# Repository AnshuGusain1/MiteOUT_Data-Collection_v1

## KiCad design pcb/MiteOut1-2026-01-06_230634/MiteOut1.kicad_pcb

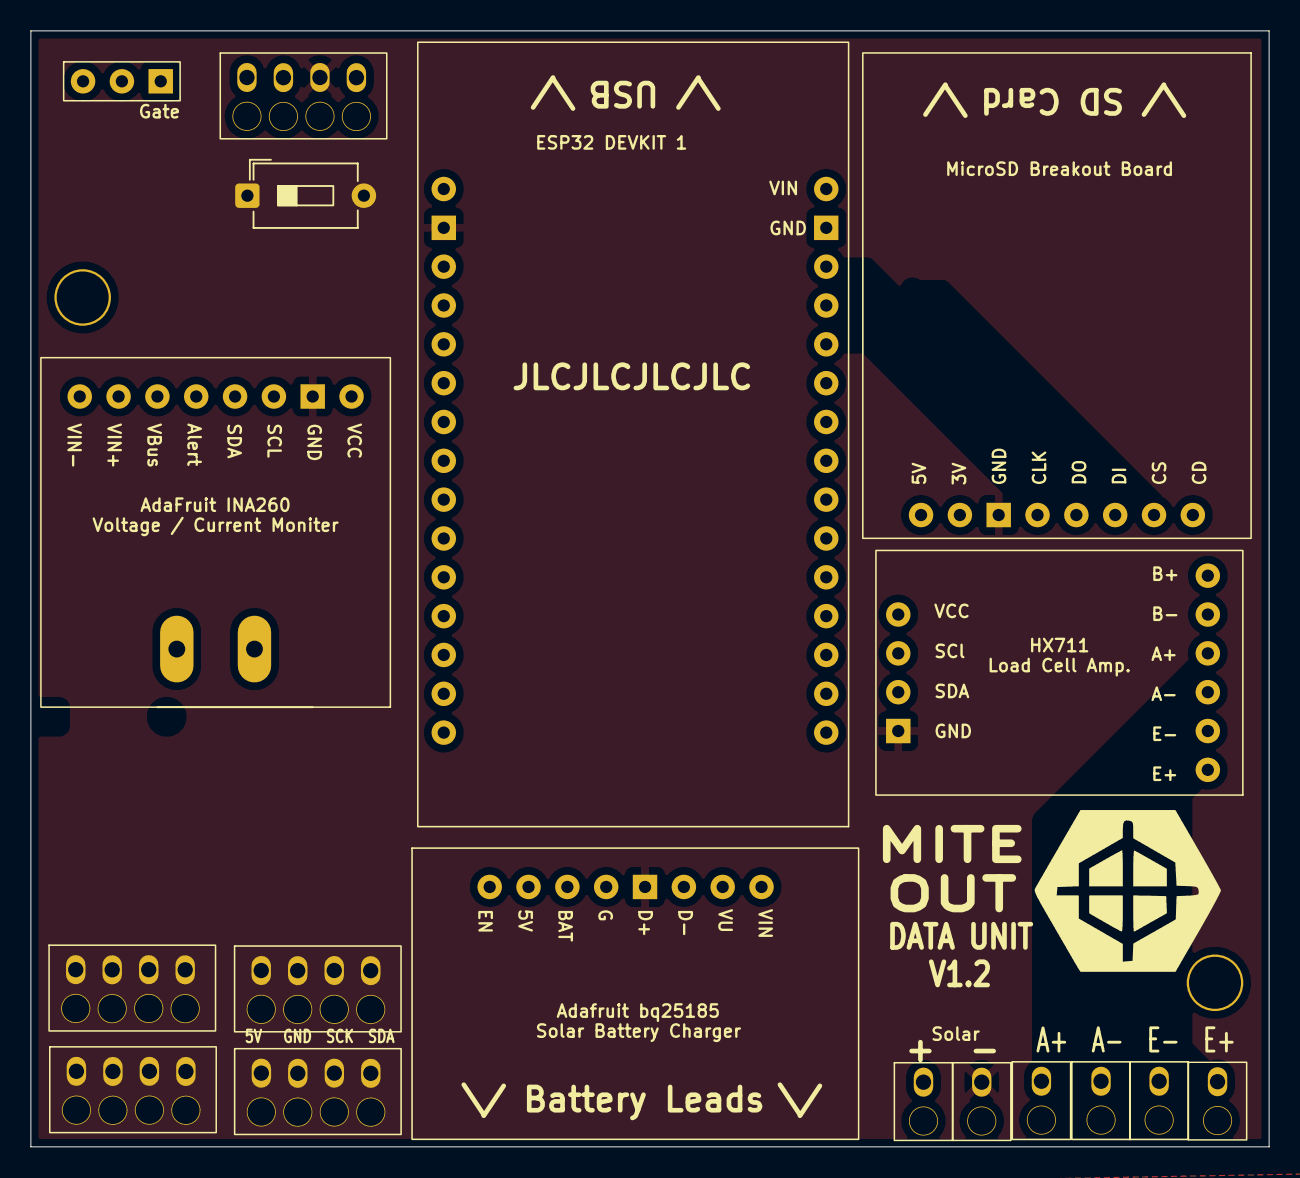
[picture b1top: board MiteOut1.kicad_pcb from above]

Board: 2 copper layers, 81.0 x 73.0 mm, 18 parts (0 on the bottom side), 19 nets, no tracks yet.

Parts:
BME1, BME2, BME3, BME4: Conn_01x04; 4Wire
BQ1: Charger
Clock1: Clock; 4Wire
H1: LoadCell3; throughole
H2: LoadCell1; throughole
H3: LoadCell4; throughole
H4: LoadCell2; throughole
H11: MountingHole_Pad_MP; throughole
H12: Solar -; throughole
HX711: hx711
INO1: INA
J3: Conn_02x15_Counter_Clockwise; ESP
Q1: PMOS; Mosfet
SW2: SW_SPST; SW_DIP_SPSTx01_Slide_6.7x4.1mm_W7.62mm_P2.54mm_LowProfile
U3: SDCard

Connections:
/HX711 CLK: HX711.9 (SCK), J3.9
/HX711 DT: HX711.8 (DT), J3.8
/Sensor VCC: BME1.4, BME2.4, BME3.4, BME4.4, Clock1.4 (3.3v), HX711.10 (VCC), INO1.1 (VCC), INO1.8 (VIN-)
/Wire0 SCK: BME1.2, BME2.2, Clock1.2 (SCL), INO1.3 (SCL), J3.26
/Wire0 SDA: BME1.1, BME2.1, Clock1.1 (SDA), INO1.4 (SDA), J3.29
/Wire1 SCK: BME3.2, BME4.2, J3.6, J3.7
/Wire1 SDA: BME3.1, BME4.1
GND: BME1.3, BME2.3, BME3.3, BQ1.5 (Ground), Clock1.3 (Gnd), H12.MP, HX711.7 (GND), INO1.2 (GND), J3.17, U3.6 (GND)
unnamed: BQ1.7 (5v), SW2.2 (B)
unnamed: BQ1.1 (Solar_in), H11.MP
unnamed: H2.MP, HX711.4 (A+)
unnamed: H1.MP, HX711.3 (A-)
unnamed: H3.MP, HX711.1 (E+)
unnamed: H4.MP, HX711.2 (E-)
unnamed: J3.11, U3.5 (CLK)
unnamed: J3.12, U3.4 (DO)
unnamed: J3.13, U3.3 (DI)
unnamed: J3.15, SW2.1 (A)
unnamed: J3.18, U3.2 (CS)

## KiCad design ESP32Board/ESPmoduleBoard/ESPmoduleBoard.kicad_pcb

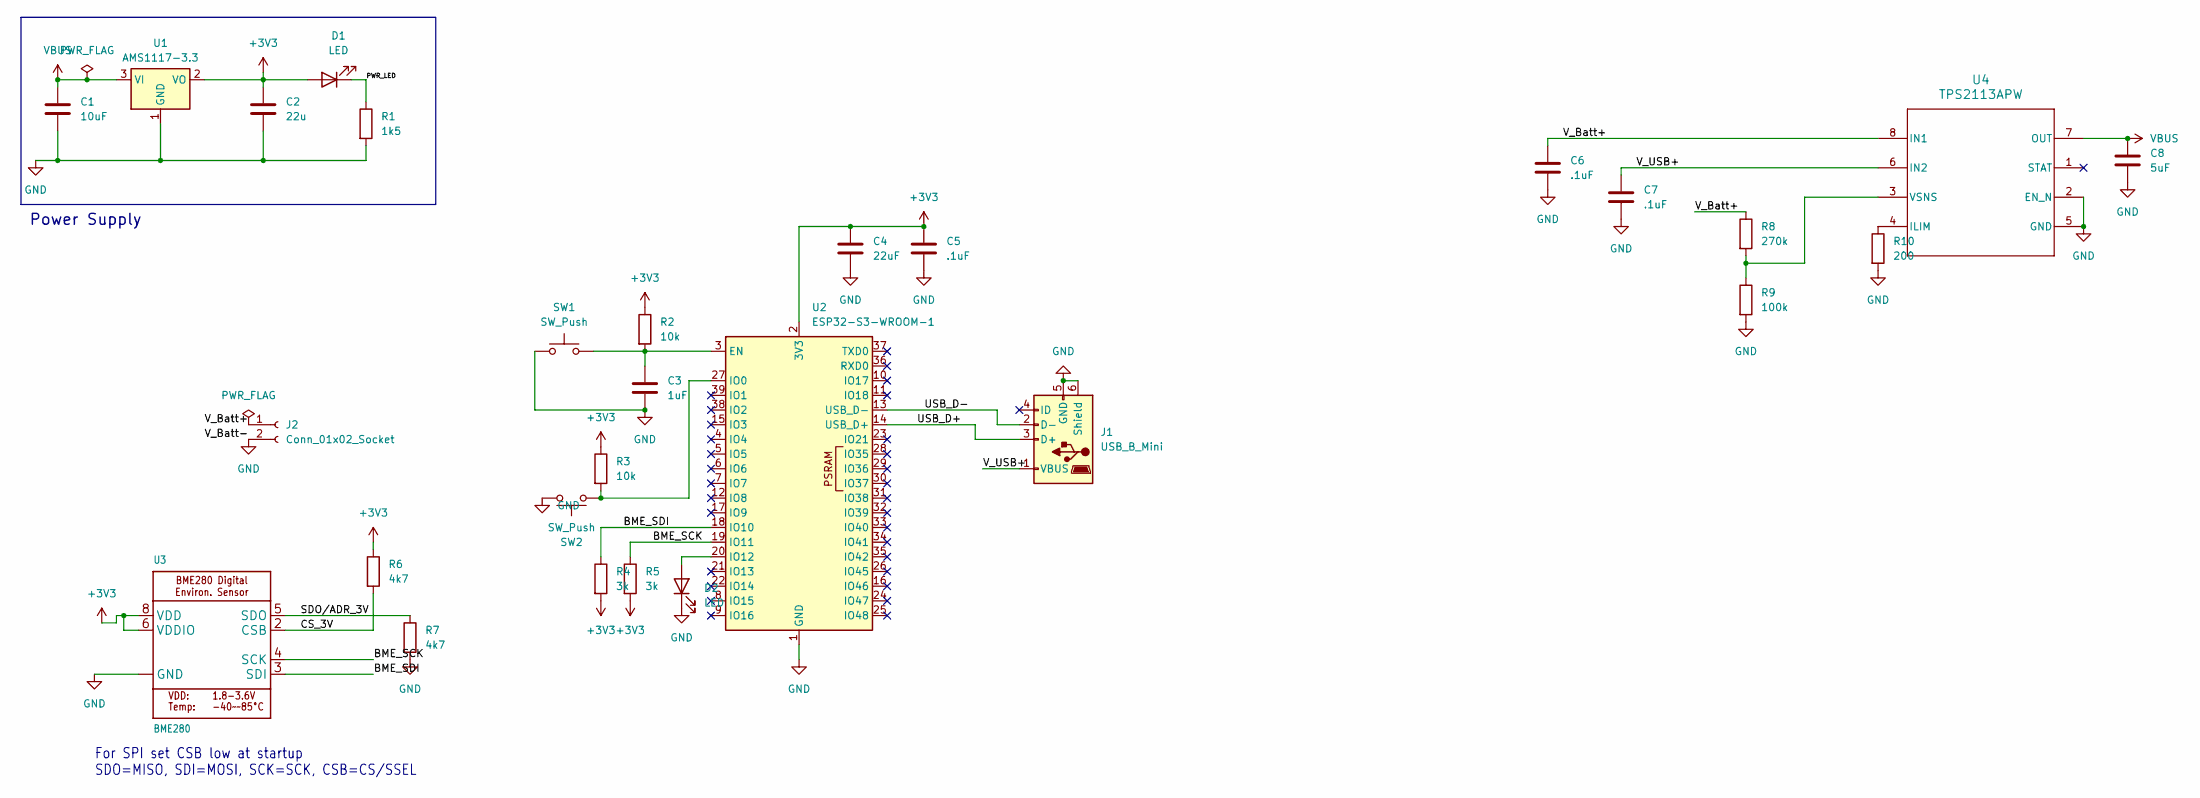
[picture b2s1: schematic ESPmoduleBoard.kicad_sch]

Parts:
C1: 10uF; C_0805_2012Metric
C2: 22u; C_0805_2012Metric
C3: 1uF; C_0402_1005Metric
C4: 22uF; C_0402_1005Metric
C5: .1uF; C_0402_1005Metric
C6, C7: .1uF; C_0201_0603Metric
C8: 5uF; C_0201_0603Metric
D1: LED; LED_0603_1608Metric
D2: LED; LED_0805_2012Metric_Pad1.15x1.40mm_HandSolder
J1: USB_B_Mini; USB_Mini-B_Lumberg_2486_01_Horizontal
J2: Conn_01x02_Socket; JST_EH_S2B-EH_1x02_P2.50mm_Horizontal
R1: 1k5; R_0402_1005Metric
R2, R3: 10k; R_0402_1005Metric
R4, R5: 3k; R_0201_0603Metric
R6, R7: 4k7; R_0402_1005Metric
R8: 270k; R_0201_0603Metric
R9: 100k; R_0201_0603Metric
R10: 200; R_0201_0603Metric
SW1, SW2: SW_Push; SW_SPST_B3U-1000P-B
U1: AMS1117-3.3; SOT-223-3_TabPin2
U2: ESP32-S3-WROOM-1
U3: BME280; Bosch_LGA-8_3x3mm_P0.8mm_ClockwisePinNumbering
U4: TPS2113APW; PW0008A_L

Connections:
+3V3: C2.1, C4.1, C5.1, D1.2 (A), R2.1, R3.1, R4.2, R5.2, R6.1, U1.2 (VO), U2.2 (3V3), U3.6 (VDDIO), U3.8 (VDD)
/BME_SCK: R5.1, U2.19 (IO11), U3.4 (SCK)
/BME_SDI: R4.1, U2.18 (IO10), U3.3 (SDI)
/CS_3V: R6.2, U3.2 (CSB)
/PWR_LED: D1.1 (K), R1.1
/SDO/ADR_3V: R7.1, U3.5 (SDO)
/USB_D+: J1.3 (D+), U2.14 (USB_D+)
/USB_D-: J1.2 (D-), U2.13 (USB_D-)
/V_Batt+: C6.1, J2.1, R8.1, U4.8 (IN1)
/V_USB+: C7.1, J1.1 (VBUS), U4.6 (IN2)
GND: C1.2, C2.2, C3.2, C4.2, C5.2, C6.2, C7.2, C8.2, D2.1 (K), J1.5 (GND), J1.6 (Shield), J2.2, R1.2, R7.2, R9.2, R10.2, SW1.1, SW2.2, U1.1 (GND), U2.1 (GND), U2.40 (GND), U2.41 (GND), U3.1 (GND), U3.7 (GND), U4.2 (EN_N), U4.5 (GND)
unnamed: D2.2 (A), U2.20 (IO12)
unnamed: C3.1, R2.2, SW1.2, U2.3 (EN)
unnamed: R3.2, SW2.1, U2.27 (IO0)
unnamed: R10.1, U4.4 (ILIM)
unnamed: R8.2, R9.1, U4.3 (VSNS)
VBUS: C1.1, C8.1, U1.3 (VI), U4.7 (OUT)

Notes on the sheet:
Power Supply
For SPI set CSB low at startup SDO=MISO, SDI=MOSI, SCK=SCK, CSB=CS/SSEL

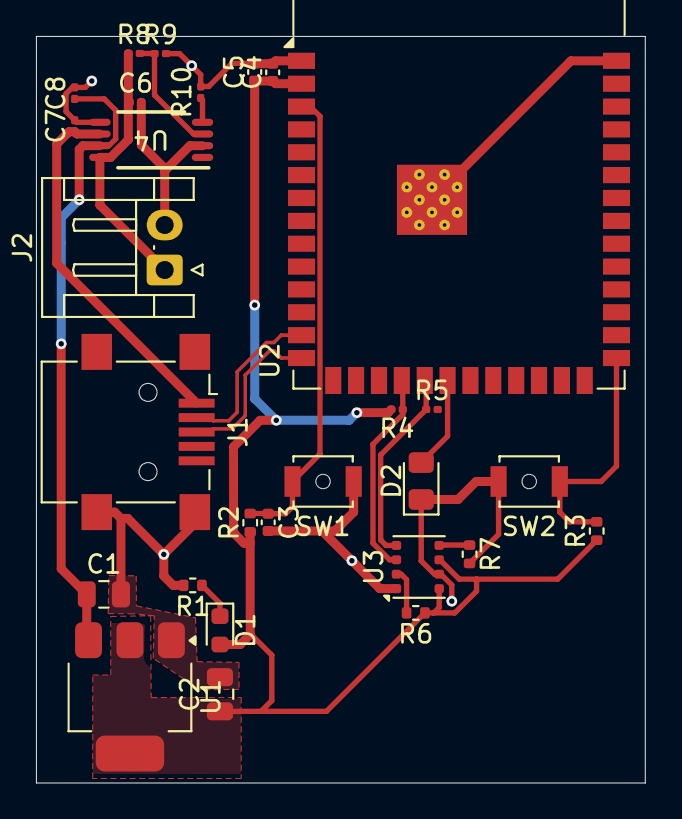
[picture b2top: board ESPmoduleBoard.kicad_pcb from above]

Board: 2 copper layers, 33.8 x 41.5 mm, 28 parts (0 on the bottom side), 17 nets.

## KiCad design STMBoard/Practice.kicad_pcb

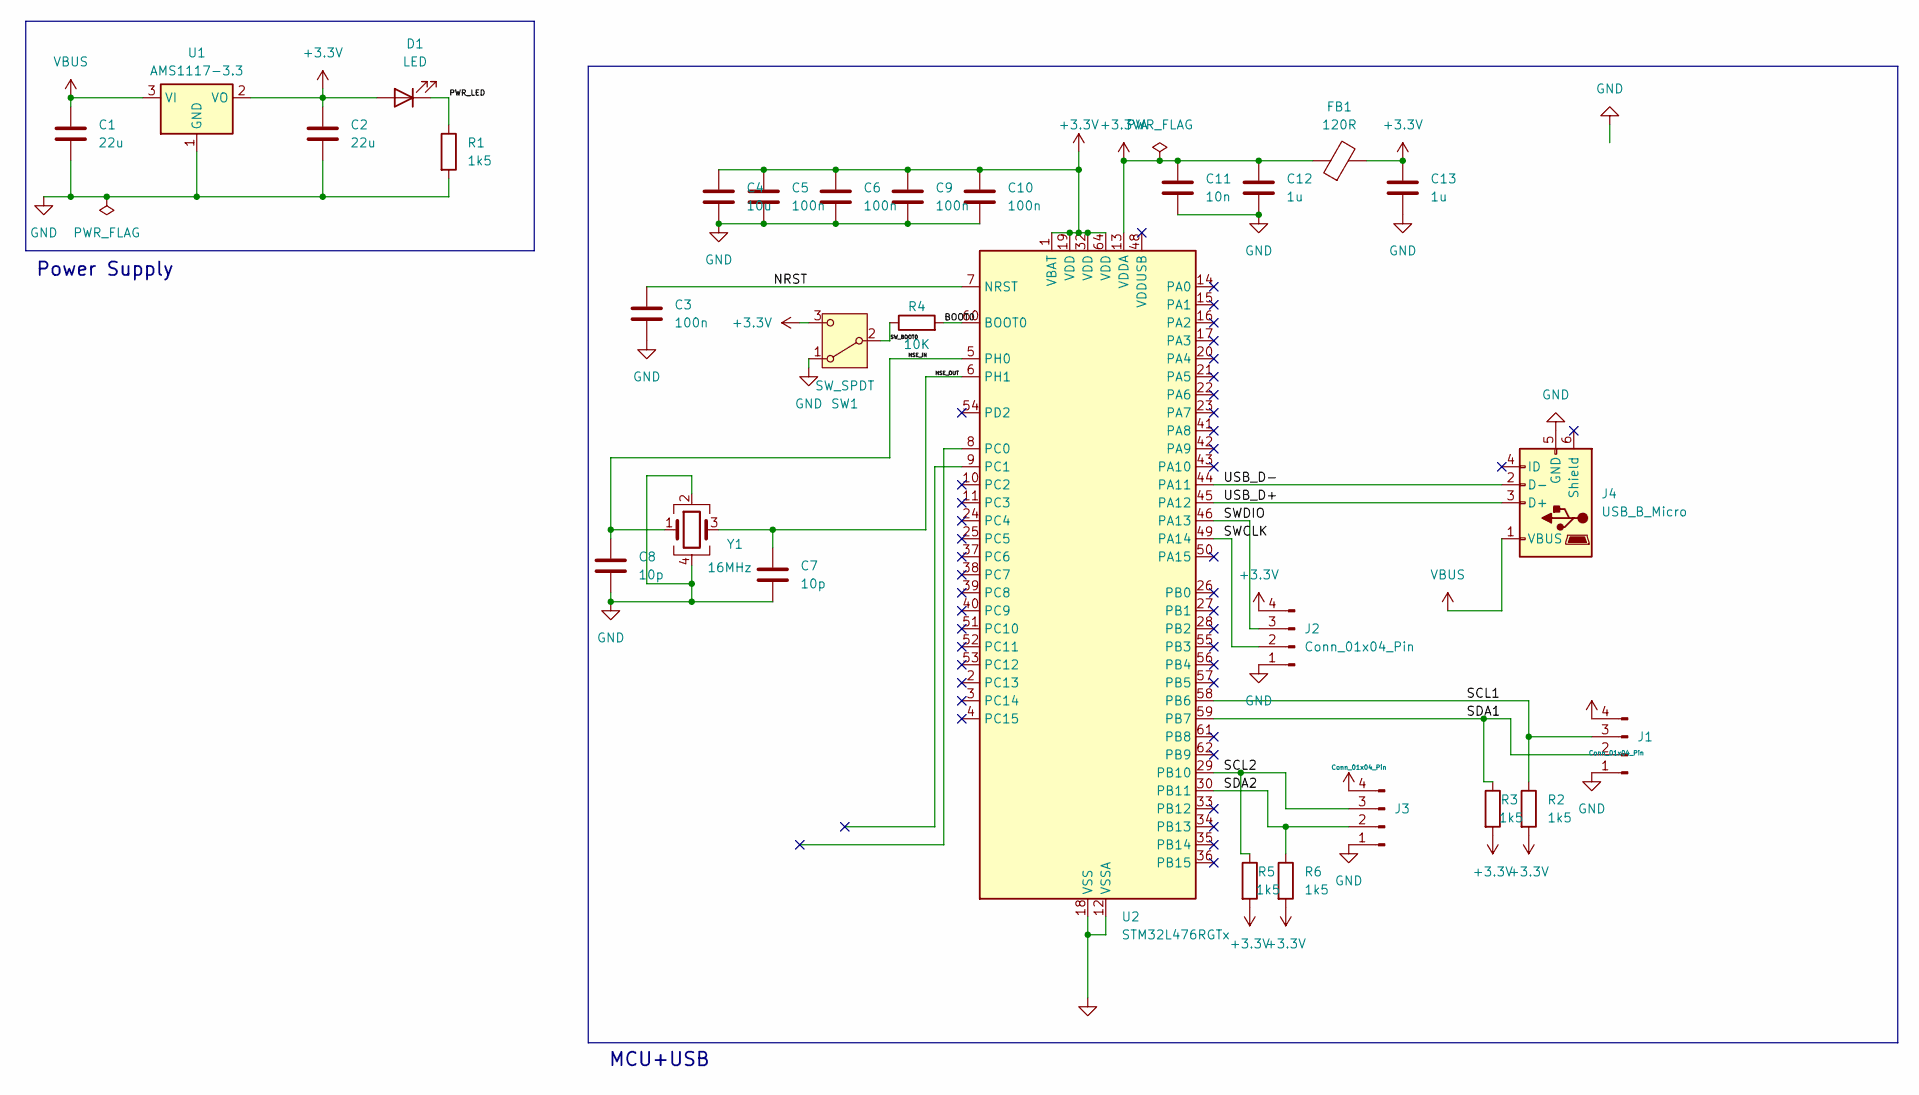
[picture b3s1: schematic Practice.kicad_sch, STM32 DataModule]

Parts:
C1, C2: 22u; C_0805_2012Metric
C3, C5, C6, C9, C10: 100n; C_0402_1005Metric
C4: 10u; C_0603_1608Metric
C7, C8: 10p; C_0402_1005Metric
C11: 10n; C_0402_1005Metric
C12, C13: 1u; C_0402_1005Metric
D1: LED; LED_0603_1608Metric
FB1: 120R; L_0603_1608Metric
J1, J2, J3: Conn_01x04_Pin; PinHeader_1x04_P2.54mm_Vertical
J4: USB_B_Micro; USB_Micro-B_Molex_47346-0001
R1, R2, R3, R5, R6: 1k5; R_0402_1005Metric
R4: 10K; R_0402_1005Metric
SW1: SW_SPDT; SW_SPDT_PCM12
U1: AMS1117-3.3; SOT-223-3_TabPin2
U2: STM32L476RGTx; LQFP-64_10x10mm_P0.5mm
Y1: 16MHz; Crystal_SMD_3225-4Pin_3.2x2.5mm_HandSoldering

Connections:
+3.3V: C2.1, C4.1, C5.1, C6.1, C9.1, C10.1, C13.1, D1.2 (A), FB1.2, J1.4, J2.4, J3.4, R2.2, R3.2, R5.2, R6.2, SW1.3 (C), U1.2 (VO), U2.1 (VBAT), U2.19 (VDD), U2.32 (VDD), U2.64 (VDD)
+3.3VA: C11.1, C12.1, FB1.1, U2.13 (VDDA)
/BOOT0: R4.2, U2.60 (BOOT0)
/HSE_IN: C8.1, U2.5 (PH0), Y1.1
/HSE_OUT: C7.1, U2.6 (PH1), Y1.3
/NRST: C3.1, U2.7 (NRST)
/PWR_LED: D1.1 (K), R1.1
/SCL1: J1.3, R2.1, U2.58 (PB6)
/SCL2: J3.3, R5.1, U2.29 (PB10)
/SDA1: J1.2, R3.1, U2.59 (PB7)
/SDA2: J3.2, R6.1, U2.30 (PB11)
/SWCLK: J2.2, U2.49 (PA14)
/SWDIO: J2.3, U2.46 (PA13)
/SW_BOOT0: R4.1, SW1.2 (B)
/USB_D+: J4.3 (D+), U2.45 (PA12)
/USB_D-: J4.2 (D-), U2.44 (PA11)
GND: C1.2, C2.2, C3.2, C4.2, C5.2, C6.2, C7.2, C8.2, C9.2, C10.2, C11.2, C12.2, C13.2, J1.1, J2.1, J3.1, J4.5 (GND), R1.2, SW1.1 (A), U1.1 (GND), U2.12 (VSSA), U2.18 (VSS), U2.31 (VSS), U2.47 (VSS), U2.63 (VSS), Y1.2, Y1.4
VBUS: C1.1, J4.1 (VBUS), U1.3 (VI)

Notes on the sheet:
Power Supply
MCU+USB

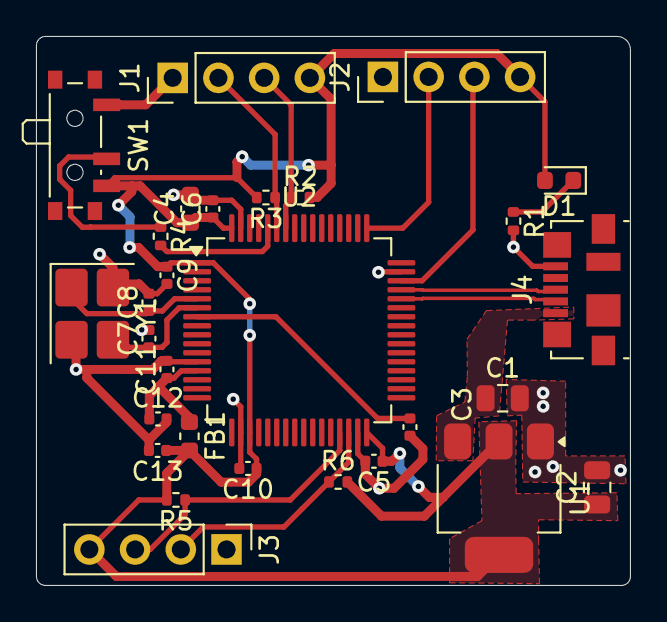
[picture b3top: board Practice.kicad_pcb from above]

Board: 2 copper layers, 33.0 x 30.5 mm, 29 parts (0 on the bottom side), 18 nets.

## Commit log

2025-06-03 first commision of PCB and schematics
2025-06-03 first version?
2025-06-13 added SD and wifi support
2025-06-13 removed PCB prototyoping files
2026-01-07 add pcb
2026-01-07 going to bed before the 10a
2026-01-09 STMBoard is the stm-based PCB. TestNucleo is the learning folder for the nucleo board.
2026-01-14 working on esp board
2026-01-23 gitignore plus test push
2026-01-23 cleaning
2026-01-23 cleaning dsstore again
2026-01-23 final changes to pcb
2026-01-28 pcb changes
